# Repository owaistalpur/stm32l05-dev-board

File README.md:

# STM32L052K6T6 Development Board

A compact development board centered around the STM32L052K6T6 microcontroller, an ARM Cortex-M0+ based MCU optimized for low power applications.

## Board Features
- STM32L052K6T6 microcontroller (32-bit ARM Cortex-M0+)
- USB connectivity for programming and power
- 3.3V LDO voltage regulator (U2)
- User button (USR BTN) for input
- Reset button for system reset
- Multiple interface headers:
  - SPI interface pins (PA3-PA7, MISO, MOSI, SCK)
  - USART interface
  - GPIO pins
  - SWD programming/debug interface
- Power options: USB
- Power LED (D1)
- Usr Leds (D2, D3)
- Supporting passive components (resistors and capacitors)

## Applications
This development platform is ideal for:
- Low-power embedded applications
- IoT device prototyping
- Battery-operated devices
- Learning STM32 microcontroller programming

## Board Version
Version 1.0 (06/03/2025)

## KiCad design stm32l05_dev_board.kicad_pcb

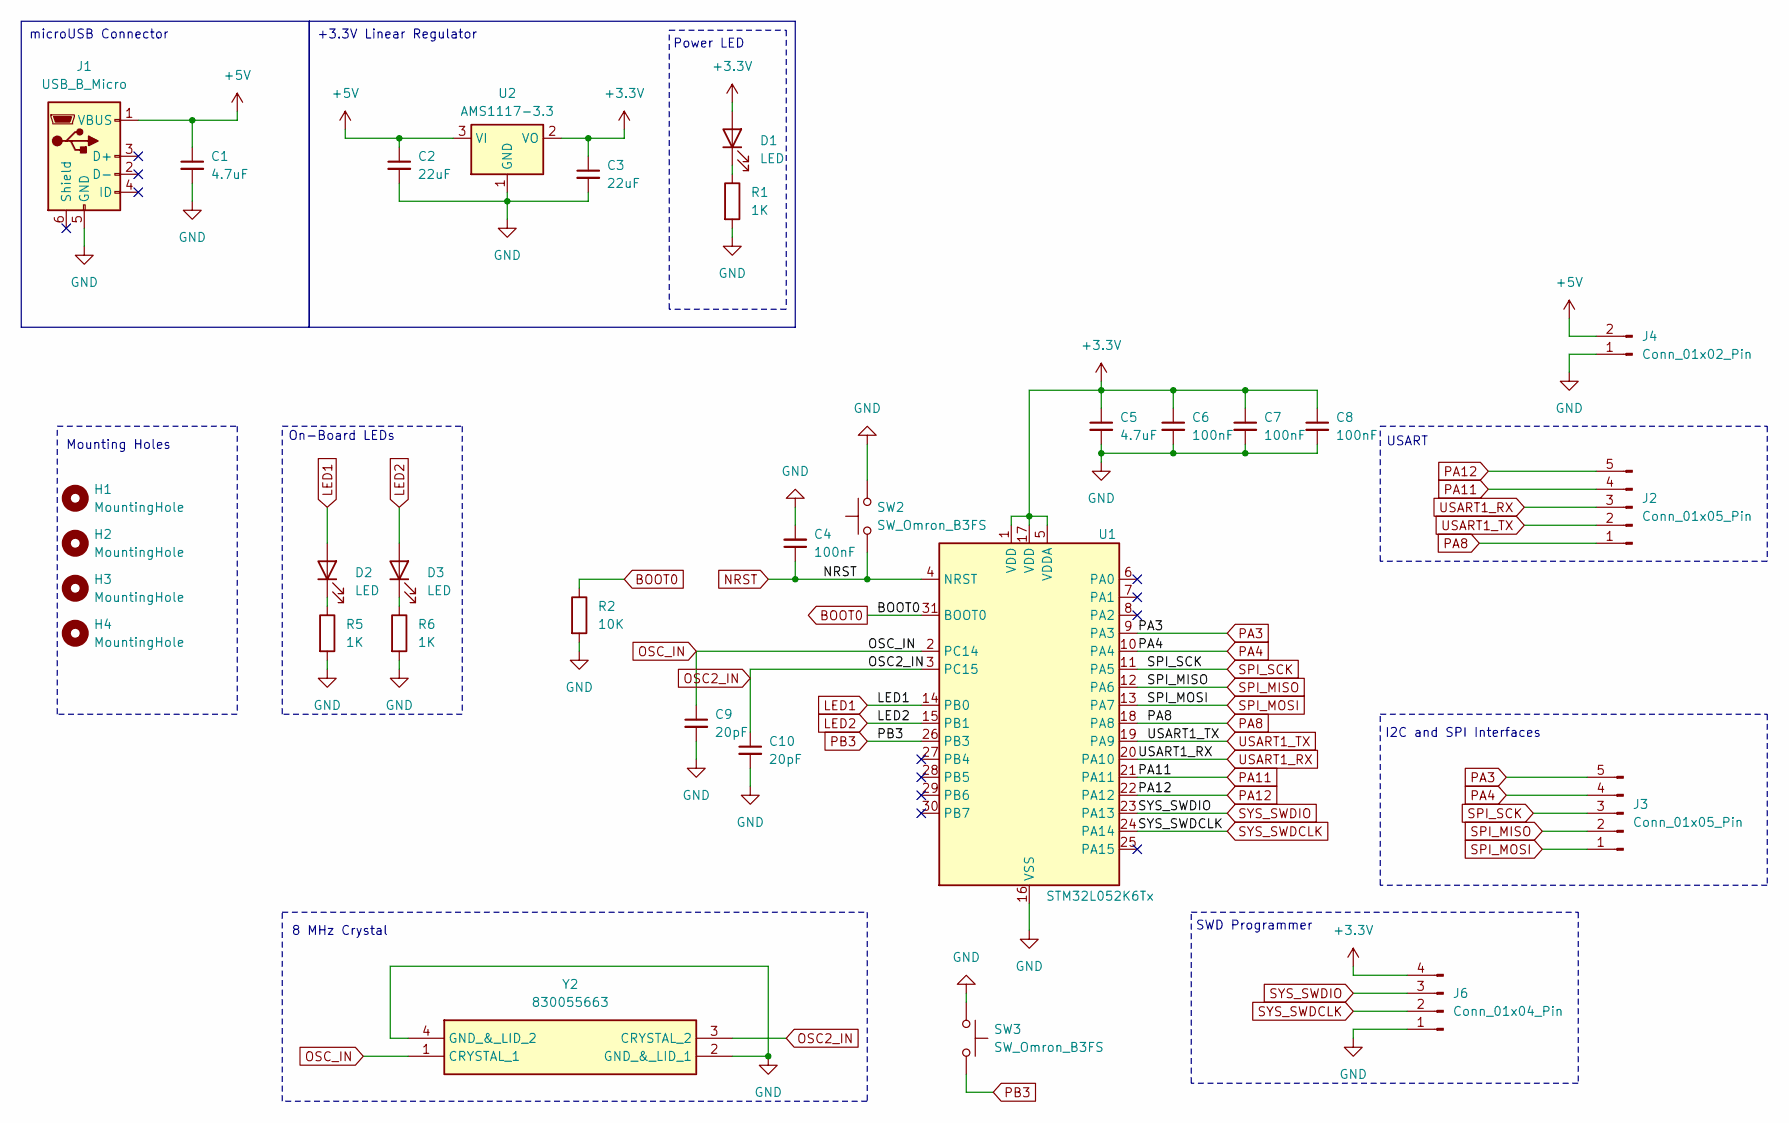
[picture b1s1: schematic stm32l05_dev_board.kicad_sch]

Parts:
C1, C5: 4.7uF; C_0603_1608Metric
C2, C3: 22uF; C_0805_2012Metric
C4, C6, C7, C8: 100nF; C_0402_1005Metric
C9, C10: 20pF; C_0402_1005Metric
D1, D2, D3: LED; LED_0603_1608Metric
H1, H2, H3, H4: MountingHole; MountingHole_2.2mm_M2_DIN965
J1: USB_B_Micro; USB_Micro-AB_Molex_47590-0001
J2, J3: Conn_01x05_Pin; PinHeader_1x05_P2.54mm_Vertical
J4: Conn_01x02_Pin; PinHeader_1x02_P2.54mm_Vertical
J6: Conn_01x04_Pin; PinHeader_1x04_P2.54mm_Vertical
R1, R5, R6: 1K; R_0402_1005Metric
R2: 10K; R_0402_1005Metric
SW2, SW3: SW_Omron_B3FS; SW_SPST_Omron_B3FS-100xP
U1: STM32L052K6Tx; LQFP-32_7x7mm_P0.8mm
U2: AMS1117-3.3; SOT-223-3_TabPin2
Y2: 830055663; Crystal_SMD_EuroQuartz_MJ-4Pin_5.0x3.2mm; Manufacturer_Part_Number 830055663; Mouser Part Number 710-830055663

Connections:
+3.3V: C3.1, C5.1, C6.1, C7.1, C8.1, D1.2 (A), J6.4, U1.1 (VDD), U1.5 (VDDA), U1.17 (VDD), U2.2 (VO)
+5V: C1.1, C2.1, J1.1 (VBUS), J4.2, U2.3 (VI)
BOOT0: R2.1, U1.31 (BOOT0)
GND: C1.2, C2.2, C3.2, C4.2, C5.2, C6.2, C7.2, C8.2, C9.2, C10.2, J1.5 (GND), J4.1, J6.1, R1.2, R2.2, R5.2, R6.2, SW2.2, SW3.1, U1.16 (VSS), U1.32 (VSS), U2.1 (GND), Y2.2 (GND_&_LID_1), Y2.4 (GND_&_LID_2)
LED1: D2.2 (A), U1.14 (PB0)
LED2: D3.2 (A), U1.15 (PB1)
NRST: C4.1, SW2.1, U1.4 (NRST)
unnamed: D1.1 (K), R1.1
unnamed: D2.1 (K), R5.1
unnamed: D3.1 (K), R6.1
OSC2_IN: C10.1, U1.3 (PC15), Y2.3 (CRYSTAL_2)
OSC_IN: C9.1, U1.2 (PC14), Y2.1 (CRYSTAL_1)
PA3: J3.5, U1.9 (PA3)
PA4: J3.4, U1.10 (PA4)
PA8: J2.1, U1.18 (PA8)
PA11: J2.4, U1.21 (PA11)
PA12: J2.5, U1.22 (PA12)
PB3: SW3.2, U1.26 (PB3)
SPI_MISO: J3.2, U1.12 (PA6)
SPI_MOSI: J3.1, U1.13 (PA7)
SPI_SCK: J3.3, U1.11 (PA5)
SYS_SWDCLK: J6.2, U1.24 (PA14)
SYS_SWDIO: J6.3, U1.23 (PA13)
USART1_RX: J2.3, U1.20 (PA10)
USART1_TX: J2.2, U1.19 (PA9)

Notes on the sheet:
+3.3V Linear Regulator
microUSB Connector
USART
On-Board LEDs
I2C and SPI Interfaces
Power LED
Mounting Holes
SWD Programmer
8 MHz Crystal

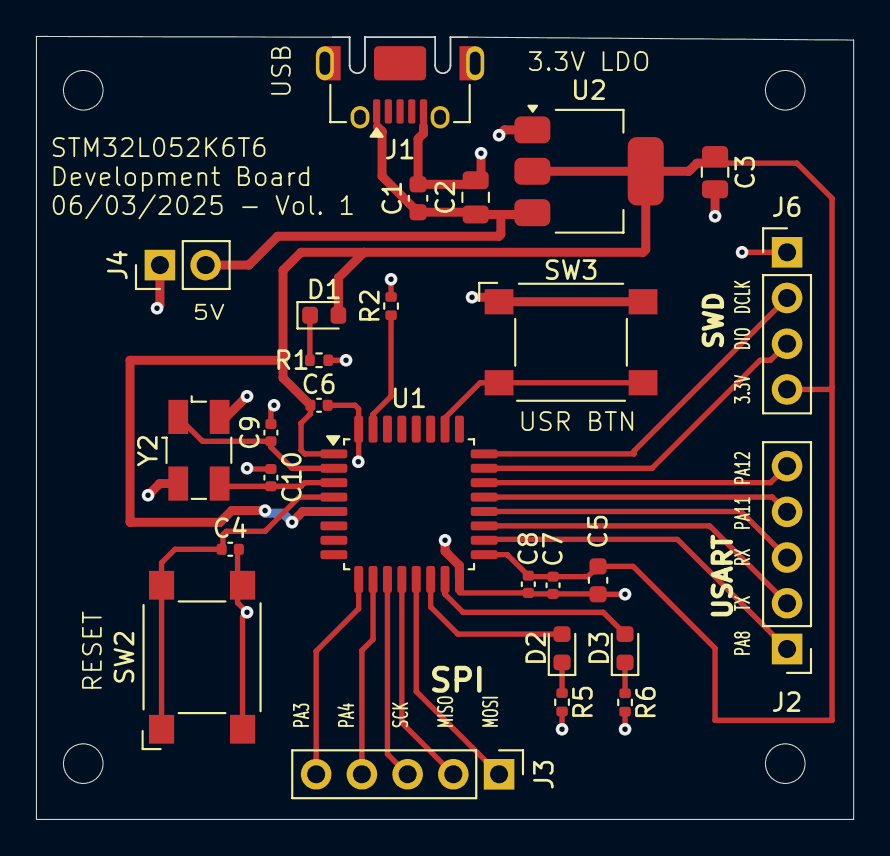
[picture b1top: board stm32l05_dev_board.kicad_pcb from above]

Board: 2 copper layers, 45.4 x 43.5 mm, 31 parts (0 on the bottom side), 25 nets.
